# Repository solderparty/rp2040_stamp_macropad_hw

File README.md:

# RP2040 Stamp MacroPad (Flux Project)

Just add switches and key caps and you have a 3x4 MacroPad powered by the RP2040 Stamp, each key footprint includes a individually addressable **NeoPixel**, the board also comes with a **1.3" 128x64 OLED**, **three function buttons**, and extra GPIOs on an **optional header**. 

The board features a 3-in-1 combo RP2040 Stamp footprint, meaning you can solder the Stamp directly using the SMD pads, use 2mm pin headers, or using our FlexyPins!

You can program it using Arduino or CircuitPython.

# What does "Flux Project" mean?

At Solder Party, we always want to get interesting products in people's hands. However, releasing a product is no easy feat, we need to make sure everything is polished, provide documentation, examples, and extensive support.

With Flux, we want to streamline the process a bit, get fun projects into everyone's hands quicker.

Flux projects are more experimental in nature. While they are tested and verified, the documentation might not be fully there, and the examples might be very basic. 
Flux projects are targeted at people who are not scared to put a bit of extra work into getting the project to where they want it to end up.
These projects are also produced in smaller quantities, there is no guarantee there will be more produced in the future. Even if there is a new batch, it might differ from the initial version. 

These projects are in constant Flux, so to speak.

If there is enough interest, a Flux project might become a fully-fledged Solder Party product in the future, but there is no guarantee.

# Links

For more information visit https://flux.solder.party/

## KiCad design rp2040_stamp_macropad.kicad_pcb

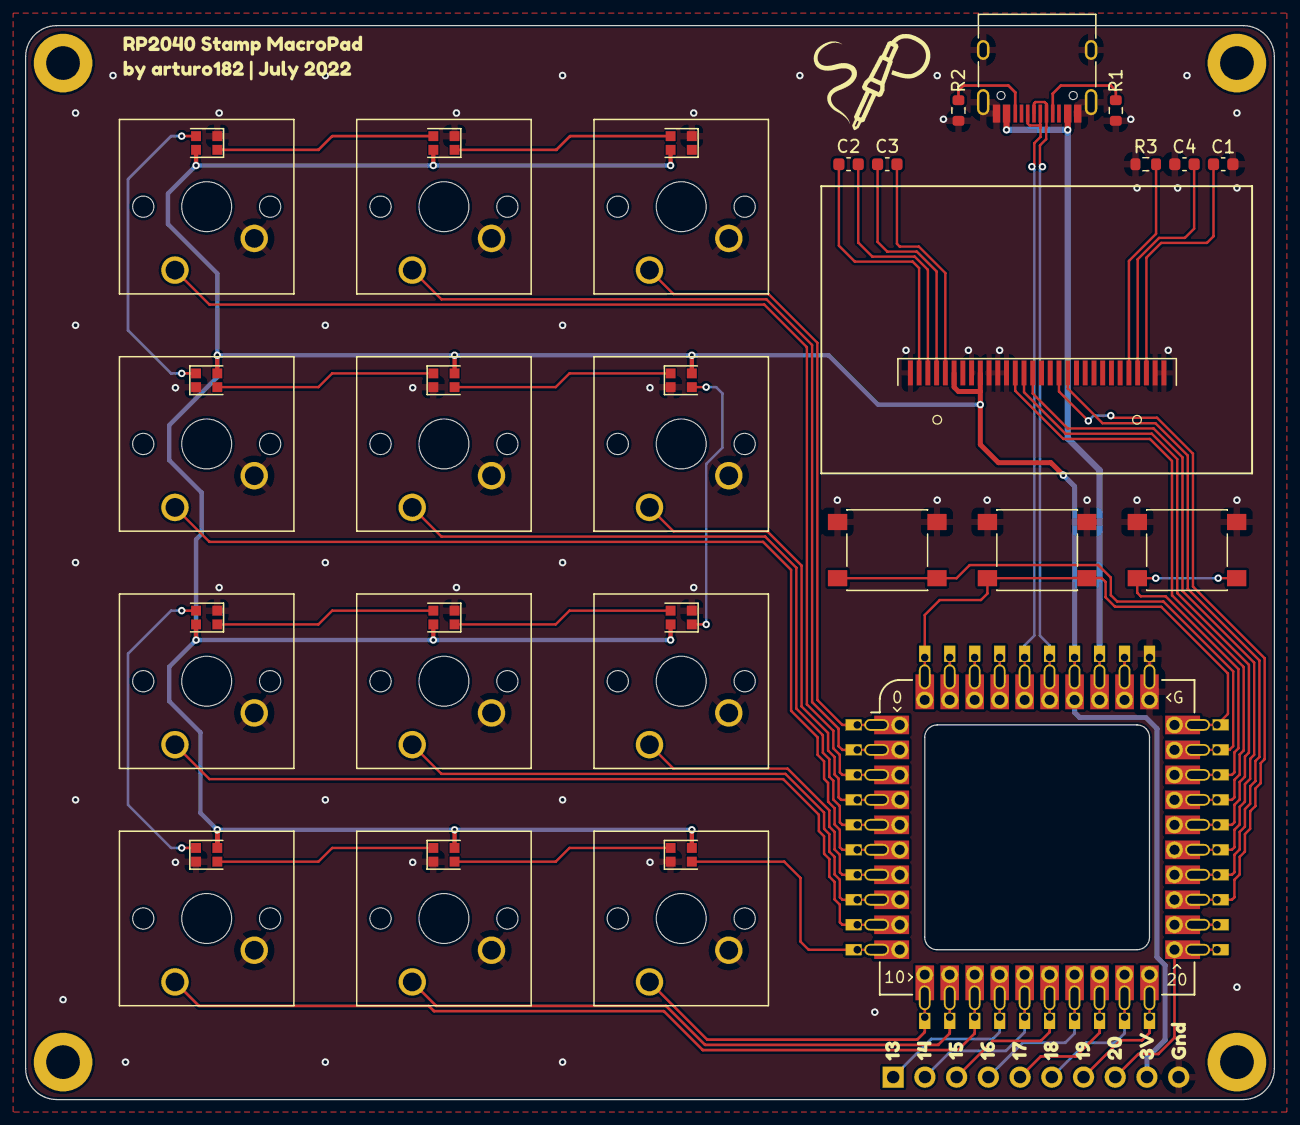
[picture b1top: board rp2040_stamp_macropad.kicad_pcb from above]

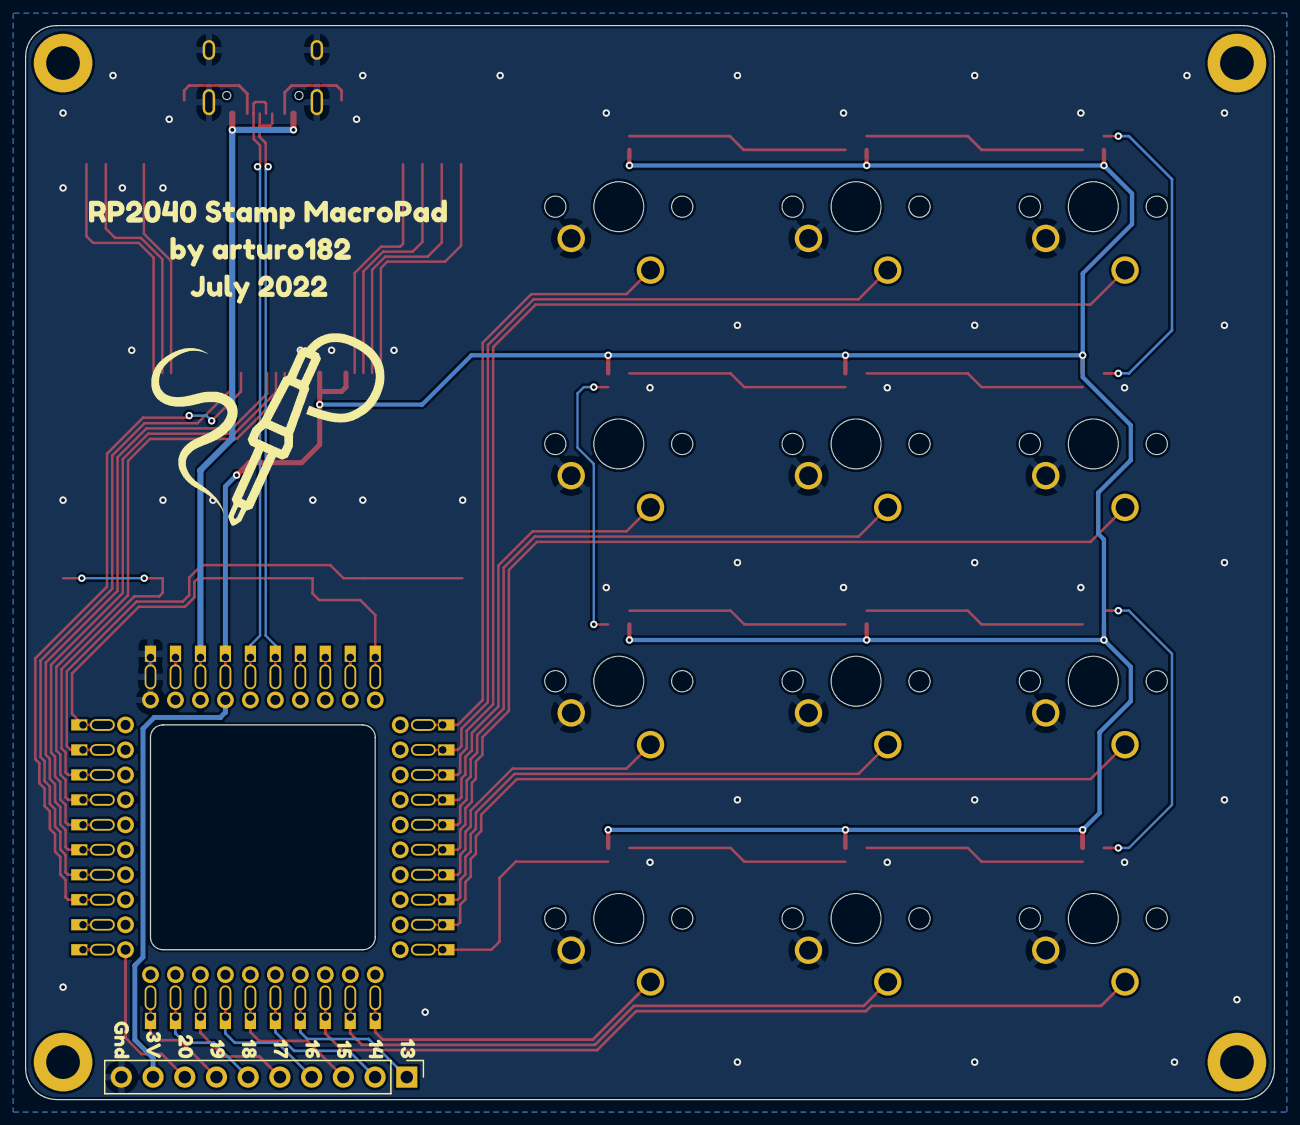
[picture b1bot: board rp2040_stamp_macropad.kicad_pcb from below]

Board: 2 copper layers, 100.0 x 86.0 mm, 60 parts (12 on the bottom side), 54 nets.

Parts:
C1, C2, C3, C4: 1uF; C_0603_1608Metric
D1, D2, D3, D4, D5, D6, D7, D8, D9, D10, D11, D12: WS2812B-2020
DS1: OLED-128O064D
J1: USB_C_Receptacle_USB2.0; USB_C_Receptacle_HRO_TYPE-C-31-M-12
J2: Conn_GPIOs; PinHeader_1x10_P2.54mm_Vertical
R1, R2: 5.1K; R_0603_1608Metric
R3: 390K; R_0603_1608Metric
SW1, SW2, SW3, SW4, SW5, SW6, SW7, SW8, SW9, SW10, SW11, SW12: SW_SPST; SW_Cherry_MX_1.00u_PCB
SW13: SW_LEFT; SW_SPST_PTS645
SW14: SW_CENTER; SW_SPST_PTS645
SW15: SW_RIGHT; SW_SPST_PTS645
U1: RP2040_Stamp; RP2040_Stamp_FlexyPin
kibuzzard-62C6D91C: G***; kibuzzard-62C6D91C
kibuzzard-62C6DD16: G***; kibuzzard-62C6DD16
kibuzzard-62DF06D5, kibuzzard-62DF06D5#2: G***; kibuzzard-62DF06D5
kibuzzard-62DF06DC, kibuzzard-62DF06DC#2: G***; kibuzzard-62DF06DC
kibuzzard-62DF061F, kibuzzard-62DF061F#2: G***; kibuzzard-62DF061F
kibuzzard-62DF063C, kibuzzard-62DF063C#2: G***; kibuzzard-62DF063C
kibuzzard-62DF064B, kibuzzard-62DF064B#2: G***; kibuzzard-62DF064B
kibuzzard-62DF0636, kibuzzard-62DF0636#2: G***; kibuzzard-62DF0636
kibuzzard-62DF0641, kibuzzard-62DF0641#2: G***; kibuzzard-62DF0641
kibuzzard-62DF0644, kibuzzard-62DF0644#2: G***; kibuzzard-62DF0644
kibuzzard-62DF0648, kibuzzard-62DF0648#2: G***; kibuzzard-62DF0648
kibuzzard-62DF0650, kibuzzard-62DF0650#2: G***; kibuzzard-62DF0650

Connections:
+3.3V: D1.4 (VDD), D2.4 (VDD), D3.4 (VDD), D4.4 (VDD), D5.4 (VDD), D6.4 (VDD), D7.4 (VDD), D8.4 (VDD), D9.4 (VDD), D10.4 (VDD), D11.4 (VDD), D12.4 (VDD), DS1.6 (VBAT), DS1.9 (VDD), J2.9, U1.34 (3.3V)
+5V: J1.A4 (VBUS), J1.A9 (VBUS), J1.B4 (VBUS), J1.B9 (VBUS), U1.33 (5V)
/BTN1: SW1.1 (A), U1.3 (GPIO2)
/BTN2: SW2.1 (A), U1.2 (GPIO1)
/BTN3: SW3.1 (A), U1.1 (GPIO0)
/BTN4: SW4.1 (A), U1.6 (GPIO5)
/BTN5: SW5.1 (A), U1.5 (GPIO4)
/BTN6: SW6.1 (A), U1.4 (GPIO3)
/BTN7: SW7.1 (A), U1.9 (GPIO8)
/BTN8: SW8.1 (A), U1.8 (GPIO7)
/BTN9: SW9.1 (A), U1.7 (GPIO6)
/BTN10: SW10.1 (A), U1.13 (GPIO12)
/BTN11: SW11.1 (A), U1.12 (GPIO11)
/BTN12: SW12.1 (A), U1.11 (GPIO10)
/BTN_CENTER: SW14.1 (A), U1.30 (GPIO29), U1.40 (BOOTSEL)
/BTN_LEFT: SW13.1 (A), U1.29 (GPIO28)
/BTN_RIGHT: SW15.1 (A), U1.28 (GPIO27)
/GPIO13: J2.1, U1.14 (GPIO13)
/GPIO14: J2.2, U1.15 (GPIO14)
/GPIO15: J2.3, U1.16 (GPIO15)
/GPIO16: J2.4, U1.17 (GPIO16)
/GPIO17: J2.5, U1.18 (GPIO17)
/GPIO18: J2.6, U1.19 (GPIO18)
/GPIO19: J2.7, U1.20 (GPIO19)
/GPIO20: J2.8, U1.21 (GPIO20)
/LCD_CLK: DS1.18 (D0), U1.23 (GPIO22)
/LCD_CS: DS1.13 (~CS), U1.27 (GPIO26)
/LCD_DC: DS1.15 (D/~C), U1.25 (GPIO24)
/LCD_MOSI: DS1.19 (D1), U1.24 (GPIO23)
/LCD_RST: DS1.14 (~RES), U1.26 (GPIO25)
/NEOPIXEL: D1.3 (DIN), U1.10 (GPIO9)
/USB_D+: J1.A6 (D+), J1.B6 (D+), U1.36 (USB_D+)
/USB_D-: J1.A7 (D-), J1.B7 (D-), U1.35 (USB_D-)
GND: C1.1, C4.2, D1.2 (VSS), D2.2 (VSS), D3.2 (VSS), D4.2 (VSS), D5.2 (VSS), D6.2 (VSS), D7.2 (VSS), D8.2 (VSS), D9.2 (VSS), D10.2 (VSS), D11.2 (VSS), D12.2 (VSS), DS1.1 (GND), DS1.8 (VSS), DS1.10 (BS0), DS1.11 (BS1), DS1.12 (BS2), DS1.29 (VLSS), DS1.30 (GND), J1.A1 (GND), J1.A12 (GND), J1.B1 (GND), J1.B12 (GND), J1.S1 (SHIELD), J2.10, R1.2, R2.2, R3.2, SW1.2 (B), SW2.2 (B), SW3.2 (B), SW4.2 (B), SW5.2 (B), SW6.2 (B), SW7.2 (B), SW8.2 (B), SW9.2 (B), SW10.2 (B), SW11.2 (B), SW12.2 (B), SW13.2 (B), SW14.2 (B), SW15.2 (B), U1.31 (GND)
unnamed: C1.2, DS1.28 (VCC)
unnamed: C2.1, DS1.2 (C2N)
unnamed: C2.2, DS1.3 (C2P)
unnamed: C3.1, DS1.4 (C1P)
unnamed: C3.2, DS1.5 (C1N)
unnamed: C4.1, DS1.27 (VCOMH)
unnamed: D1.1 (DOUT), D2.3 (DIN)
unnamed: D2.1 (DOUT), D3.3 (DIN)
unnamed: D3.1 (DOUT), D4.3 (DIN)
unnamed: D4.1 (DOUT), D5.3 (DIN)
unnamed: D5.1 (DOUT), D6.3 (DIN)
unnamed: D6.1 (DOUT), D7.3 (DIN)
unnamed: D7.1 (DOUT), D8.3 (DIN)
unnamed: D8.1 (DOUT), D9.3 (DIN)
unnamed: D10.1 (DOUT), D11.3 (DIN)
unnamed: D9.1 (DOUT), D10.3 (DIN)
unnamed: D11.1 (DOUT), D12.3 (DIN)
unnamed: DS1.26 (IREF), R3.1
unnamed: J1.A5 (CC1), R1.1
unnamed: J1.B5 (CC2), R2.1

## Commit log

2022-07-07 Rev 1
2022-09-22 Rev 2
